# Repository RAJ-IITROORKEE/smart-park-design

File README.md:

<div align="center">

# SmartPark

### A compact ceiling-mounted parking node

XIAO ESP32S3 · Wio-SX1262 LoRa · HC-SR04 · LiPo · optional OLED

**Rev D indoor pilot — digitally checked, awaiting physical validation**

[Download PCB](https://github.com/RAJ-IITROORKEE/smart-park-design/releases/download/revd-pilot/SmartPark-RevD-PCB-Fabrication.zip) · [Download case](https://github.com/RAJ-IITROORKEE/smart-park-design/releases/download/revd-pilot/Case-Print-Files.zip) · [Build guide](docs/SmartPark-RevD-Build-Guide.md) · [3D models](previews/README.md)

**[Watch the product video](https://github.com/RAJ-IITROORKEE/smart-park-design/raw/refs/heads/main/media/showcase/brag.mp4)**

</div>

SmartPark is a hardware design for an indoor parking-bay occupancy node. Mount it above the bay with the ultrasonic faces pointing down; parking firmware can compare the measured distance with an empty-bay baseline and report changes over LoRa. The target installation height is up to **2.8 m**.

This repository contains the carrier PCB, two enclosure variants, editable CAD, fabrication exports and illustrated assembly guides. **Parking firmware, a LoRa gateway and a dashboard are not included.**

## The finished design

| With OLED | Without OLED |
|:---:|:---:|
|  |  |
| Aisle-facing 0.96-inch display and bottom status light pipe | Closed front panel and programmable RGB indication |
| [GLB](previews/04-complete-product/product_oled.glb) · [STEP](previews/04-complete-product/product_oled.step) | [GLB](previews/04-complete-product/product_status.glb) · [STEP](previews/04-complete-product/product_status.step) |

| Carrier PCB | Connected electronics |
|:---:|:---:|
|  |  |
| [PCB GLB](previews/01-pcb/pcb-carrier.glb) · [PCB STEP](previews/01-pcb/pcb-carrier.step) | [Stack GLB](previews/02-connected-electronics/electronics-stack.glb) · [Stack STEP](previews/02-connected-electronics/electronics-stack.step) |

**62 × 50 mm carrier** · **70 × 66 × 50.4 mm closed body** · **94 mm width including mounting ears**

The case conceals the HC-SR04 board and exposes only its two transducer faces underneath, alongside the RGB light pipe. The OLED faces the aisle. These are CAD previews of intended assembly; solder fillets, wiring and some purchased-part details are not modeled.

## Downloads

| What you need | Direct download | Read before use |
|---|---|---|
| PCB manufacturing files | **[Gerbers and drills ZIP](https://github.com/RAJ-IITROORKEE/smart-park-design/releases/download/revd-pilot/SmartPark-RevD-PCB-Fabrication.zip)** | [Board fabrication notes](docs/FABRICATION.md) |
| Case print files | **[STL and 3MF ZIP](https://github.com/RAJ-IITROORKEE/smart-park-design/releases/download/revd-pilot/Case-Print-Files.zip)** | [Part selection and assembly](docs/BUILD_AND_RELEASE.md) |
| Everything together | **[Complete RevD project ZIP](https://github.com/RAJ-IITROORKEE/smart-park-design/releases/download/revd-pilot/SmartPark-RevD-Complete.zip)** | Includes PCB sources, models, guides and videos |
| Illustrated build manual | [Word document](https://github.com/RAJ-IITROORKEE/smart-park-design/raw/refs/heads/main/docs/SmartPark-RevD-Build-Guide.docx) · [Markdown](docs/SmartPark-RevD-Build-Guide.md) | Parts, soldering, wiring, battery and firmware connections |
| Connection schematic | [PNG](outputs/schematics.png) · [PDF](outputs/schematics.pdf) · [SVG](outputs/schematic-svg/SmartMark.svg) | [GPIO map](docs/PINOUT.md) |
| Editable PCB project | [KiCad project folder](hardware) | Open SmartMark.kicad_pro |
| All 3D views | [Organized model index](previews/README.md) | Carrier, electronics, enclosure-only and complete assemblies |

[View the RevD pilot release](https://github.com/RAJ-IITROORKEE/smart-park-design/releases/tag/revd-pilot). File integrity is recorded in [SHA256SUMS.txt](SHA256SUMS.txt).

The same Gerbers serve both variants. For OLED use [BOM.csv](outputs/BOM.csv) and [SMD placements](outputs/placements-smd.csv). For no OLED use [BOM-no-OLED.csv](outputs/BOM-no-OLED.csv) and [matching placements](outputs/placements-smd-no-OLED.csv); omit J2, R8 and R9. A bare fabricated board still needs its electronic parts assembled.

## PCB front and back

| Front copper and silkscreen | Back copper and silkscreen |
|:---:|:---:|
|  |  |
| [Front SVG](previews/01-pcb/pcb-front.svg) · [Assembly SVG](previews/01-pcb/assembly-front.svg) | [Back SVG](previews/01-pcb/pcb-back.svg) · [Assembly SVG](previews/01-pcb/assembly-back.svg) |

Two copper layers, 1.6 mm FR4 and 35 µm nominal copper. **D1 RGB and C7 mount on the underside.** The back preview is mirrored to show the underside; upload fabrication Gerbers and drills unchanged.

## Components

| Qty | Component | Role | Product or ordering reference |
|:---:|---|---|---|
| 1 kit | **XIAO ESP32S3 + Wio-SX1262**, SKU 102010611 | Controller, LoRa radio and battery charging | [Seeed](https://www.seeedstudio.com/Wio-SX1262-with-XIAO-ESP32S3-p-5982.html) · [Robocraze](https://robocraze.com/products/xiao-esp32s3-wio-sx1262-kit-for-meshtastic-lora) |
| 1 | **HC-SR04** | Downward-facing ultrasonic range measurement | [Robu SKU 2444](https://robu.in/product/hc-sr04-ultrasonic-range-finder/) |
| 0 or 1 | **GoldenMorning GME12864-11 OLED** | Optional 0.96-inch 128×64 SSD1306 I²C display | [Robu SKU 617725](https://robu.in/product/0-96-inch-i2c-iic-oled-lcd-module-4pin-with-vcc-gnd-white/) |
| 1 | **Protected 1S LiPo**, target 1500 mAh | 3.7 V battery, within the 51 × 34 × 5 mm reference envelope | [Pack candidate](https://probots.co.in/lithium-ion-rechargeable-battery-3-7v-1500mah-kp-053450.html); confirm total dimensions and protection |
| 1 | **WS2812B-2020-V6**, D1 | Programmable RGB status through a light pipe | [Exact V6 pixel](https://lcscindia.com/part/WS2812B-2020-V6) |
| 1 | **TPS61099DRVR**, U2 | Switched 5 V sensor and RGB supply | [TI](https://www.ti.com/product/TPS61099) |
| 1 | **SN74LVC1G17DBVR**, U4 | Buffers the sensor ECHO into 3.3 V logic | [TI](https://www.ti.com/product/SN74LVC1G17) |
| 1 | **SN74LVC1T45DBVR**, U3 | Translates RGB data to switched 5 V | [TI](https://www.ti.com/product/SN74LVC1T45) |
| 1 | **VLS3012CX-2R2M-1**, L1 | 2.2 µH boost inductor | [TDK](https://product.tdk.com/en/search/inductor/inductor/smd/info?part_no=VLS3012CX-2R2M-1) |
| 1 set | Capacitors, resistors, sockets and cables | Carrier assembly and modular connections | [Complete parts table with links](docs/parts-and-product-links.csv) · [Electrical BOM](docs/BOM.md) |
| optional | **DFRobot FIT0601** regulated solar panel | External regulated 5 V USB input | [DFRobot](https://www.dfrobot.com/product-1774.html) · [Evelta](https://evelta.com/monocrystalline-solar-panel-5v-1a/) |

Product links are sourcing references, not guarantees of stock or sample fit. Confirm the battery, socket/header stack, sensor and display before buying a batch. U2 has a 2 × 2 mm exposed-pad package and needs a controlled reflow process.

## The enclosure

Four releasable snap clips lock the lid. The removable front panel and sensor retainers use screws. Four 4.5 mm mounting holes have **82 × 42 mm** center spacing.

| Version | Installed printed parts |
|---|---|
| **OLED — 7 parts** | base, lid, sensor_mask, sensor_retainer, light_pipe, front_oled, oled_retainer |
| **No OLED — 6 parts** | base, lid, sensor_mask, sensor_retainer, light_pipe, front_blank |
| Trial print | fit_coupon; not installed in the product |

<details>
<summary><strong>See all print parts and enclosure-only CAD</strong></summary>

- [OLED case only — GLB](previews/03-enclosure/case-oled.glb) · [STEP](previews/03-enclosure/case-oled.step)
- [No-OLED case only — GLB](previews/03-enclosure/case-no-oled.glb) · [STEP](previews/03-enclosure/case-no-oled.step)
- [Individual STL files](cad/STL) · [3MF files](cad/3MF) · [Print measurements](docs/PRINT_CHECK.md)

Start with PETG, 0.2 mm layers, a 0.4 mm nozzle and four walls. Print the coupon first, inspect supports in the slicer and keep clip gaps free. Use clear PETG or a suitable 3 mm clear rod for the light pipe. Print individual parts; complete product assemblies include electronics and are not whole-product print files.

</details>

## Power and battery

The LiPo sits **beneath the carrier PCB**, toward the front panel and next to the ultrasonic sensor. Use a protected **3.7 V single cell**, target **1500 mAh** (about 5.55 Wh nominal), within the **51 × 34 × 5 mm** reference envelope, plus 1 mm insulating foam and a nonconductive strap.

**There is no battery socket on the carrier.** Solder a matching protected-pack lead to the XIAO BAT+ and BAT− pads before mating the Wio module. Confirm polarity, PCM dimensions, pouch seals and lead clearance.

External solar support uses a **regulated 5 V USB output into XIAO USB-C**. Use solar or service USB one at a time. The XIAO is the only cell charger; the carrier contains no raw-panel input or MPPT controller.

<details>
<summary><strong>Battery placement image and runtime assumptions</strong></summary>

| Sampling interval | Modelled runtime on 1500 mAh |
|---|---:|
| Every 5 seconds | approximately 12–32 days |
| Every 10 seconds | approximately 23–61 days |

These are unmeasured scenarios with 80% usable capacity, deep sleep, brief sensing and LED flashes, OLED off or omitted, and occasional short LoRa reports. **Continuous RGB keeps the shared sensor supply on** and can reduce the modelled runtime to about 20–40 hours. Wi-Fi, continuous display, radio receive and retries also increase demand.

See [all assumptions and calculations](docs/SmartPark-RevD-Build-Guide.md#estimated-battery-runtime). Seeed lists 50 mA charging on its general XIAO page and 100 mA on the kit page; confirm the delivered board before estimating recharge time. Larger packs or an 18650 require a new fit check or case revision.

</details>

## Wiring and programming

| Function | Connection |
|---|---|
| HC-SR04 TRIG | J1 pin 2 → D0 / GPIO1 |
| HC-SR04 ECHO | J1 pin 3 → U4 buffer → D1 / GPIO2; never raw 5 V ECHO to MCU |
| Sensor supply | J1 pin 1: switched 5V_SENSOR; pin 4: GND |
| Sensor and RGB supply enable | D3 / GPIO4, active high |
| OLED | J2 pins 1 GND, 2 3V3, 3 SCL / GPIO6, 4 SDA / GPIO5 |
| Onboard RGB data | D6 / GPIO43 through U3; one WS2812B-2020-V6 |
| Firmware upload | XIAO USB-C data cable; XIAO ESP32S3 target; disconnect external solar |

Keep BOOST_EN low during startup, initialize TRIG and RGB data low, then enable the supply and wait at least 60 ms before sensing. Leave D2 / GPIO3 unused and reserve D8–D10 for Wio.

The module stack needs two 8.5 mm female sockets, 2.5 mm male header shoulders and a **0.6 mm air gap above the male plastic**, set with a removable soldering shim. Carrier-to-XIAO PCB separation is 11.6 mm; male short legs must be at least 3 mm. Use the XIAO's 14 edge pads, not Wio's radio-only outer rows.

[Full pin orientation](docs/PINOUT.md) · [Connection schematic](outputs/schematics.png) · [Step-by-step build guide](docs/SmartPark-RevD-Build-Guide.md)

## Validation and intended use

| Digital check | Retained result |
|---|---|
| Native KiCad ERC / DRC | 0 reported violations |
| Unrouted connections / schematic parity | 0 / 0 |
| Independent critical package-pin checks | 42 |
| CAD checks | 116; no failures, one unverified commodity sensor dimension assumption |
| Individual printable meshes | 9 closed meshes |
| Source and export integrity | Recorded SHA256 hashes and [delivery check](verification/delivery-check.json) |

Checks apply to the delivered rule configuration, including documented ignored categories. They do not establish physical qualification.

**RevD is an unbuilt indoor pilot.** HC-SR04 has a nominal 4 m range; it is not a 5 m or weatherproof sensor. Calibrate at the actual installation and test different vehicle roofs, adjacent bays, echo timeouts, temperature and mounting angle. Physical fit, electrical startup, RF, battery runtime, latch life and mounting strength still require first-article validation. Resolve India-specific radio settings and equipment requirements before deployment.

## Find your files

| Folder | Contents |
|---|---|
| [hardware](hardware) | Editable KiCad project, schematic, PCB and local libraries |
| [outputs](outputs) | Fabrication exports, schematic images, BOM and placement tables |
| [cad](cad) | Parametric sources, STEP, GLB, STL, 3MF and geometry checks |
| [previews](previews/README.md) | Numbered carrier, electronics, enclosure and full-product previews |
| [docs](docs) | Illustrated Word/Markdown guides, procurement, power and print notes |
| [media](media/README.md) | Showcase video, poster, animation and original recording |
| [verification](verification) | Electrical, mechanical, document and release evidence |

The short showcase was made with [/brag](https://github.com/RAJ-IITROORKEE/smart-park-design/tree/main/media/showcase) and Hyperframes using the real CAD preview images. It presents the design intent, not a demonstration of working deployed hardware.

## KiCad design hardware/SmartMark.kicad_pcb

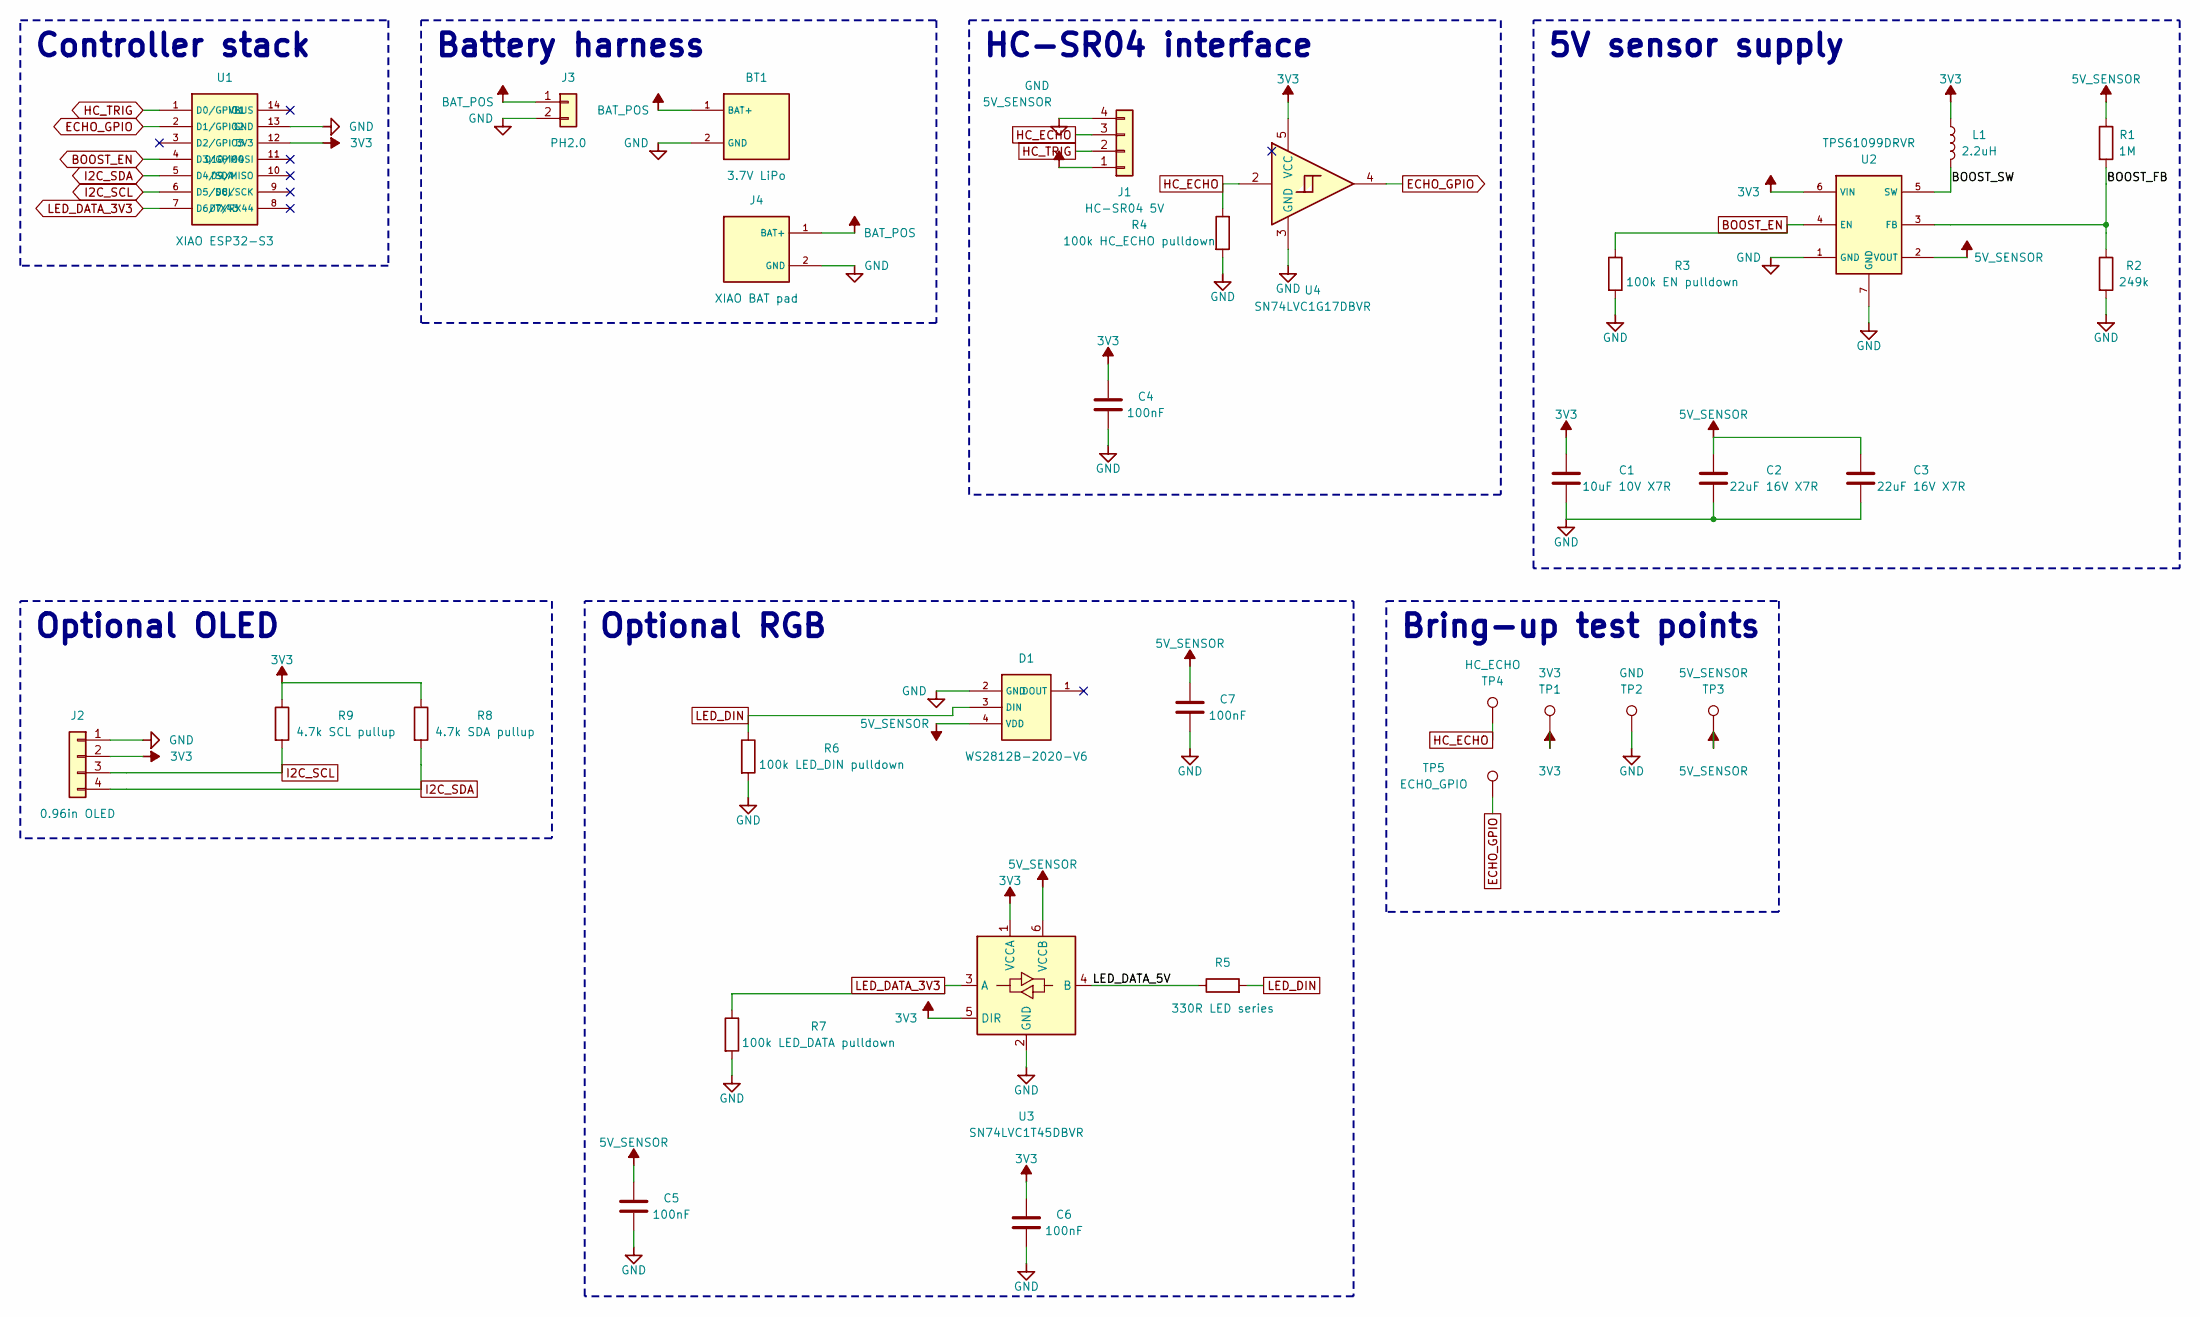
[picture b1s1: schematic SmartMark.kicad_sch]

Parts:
BT1: 3.7V LiPo
C1: 10uF 10V X7R; C_0805_2012Metric
C2, C3: 22uF 16V X7R; C_1206_3216Metric
C4, C5, C6, C7: 100nF; C_0603_1608Metric
D1: WS2812B-2020-V6; WS2812B_2020_V6
J1: HC-SR04 5V; JST_PH_B4B-PH-K_1x04_P2.00mm_Vertical
J2: 0.96in OLED; PinHeader_1x04_P2.54mm_Vertical
J3: PH2.0
J4: XIAO BAT pad
L1: 2.2uH; VLS3012CX_2R2M
R1: 1M; R_0603_1608Metric
R2: 249k; R_0603_1608Metric
R3: 100k EN pulldown; R_0603_1608Metric
R4: 100k HC_ECHO pulldown; R_0603_1608Metric
R5: 330R LED series; R_0603_1608Metric
R6: 100k LED_DIN pulldown; R_0603_1608Metric
R7: 100k LED_DATA pulldown; R_0603_1608Metric
R8: 4.7k SDA pullup; R_0603_1608Metric
R9: 4.7k SCL pullup; R_0603_1608Metric
TP1: 3V3; TestPoint_Pad_D1.0mm
TP2: GND; TestPoint_Pad_D1.0mm
TP3: 5V_SENSOR; TestPoint_Pad_D1.0mm
TP4: HC_ECHO; TestPoint_Pad_D1.0mm
TP5: ECHO_GPIO; TestPoint_Pad_D1.0mm
U1: XIAO ESP32-S3; XIAO_S3_STACK_SOCKET_2x7
U2: TPS61099DRVR; WSON-6-1EP_2x2mm_P0.65mm_EP1x1.6mm
U3: SN74LVC1T45DBVR; SOT-23-6
U4: SN74LVC1G17DBVR; SOT-23-5

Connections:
3V3: C1.1, C4.1, C6.1, J2.2, L1.1, R8.1, R9.1, TP1.1, U1.12 (3V3), U2.6 (VIN), U3.1 (VCCA), U3.5 (DIR), U4.5 (VCC)
5V_SENSOR: C2.1, C3.1, C5.1, C7.1, D1.4 (VDD), J1.1, R1.1, TP3.1, U2.2 (VOUT), U3.6 (VCCB)
/BOOST_FB: R1.2, R2.1, U2.3 (FB)
/BOOST_SW: L1.2, U2.5 (SW)
/LED_DATA_5V: R5.1, U3.4 (B)
BOOST_EN: R3.1, U1.4 (D3/GPIO4), U2.4 (EN)
ECHO_GPIO: TP5.1, U1.2 (D1/GPIO2), U4.4
GND: BT1.2 (GND), C1.2, C2.2, C3.2, C4.2, C5.2, C6.2, C7.2, D1.2 (GND), J1.4, J2.1, J3.2, J4.2 (GND), R2.2, R3.2, R4.2, R6.2, R7.2, TP2.1, U1.13 (GND), U2.1 (GND), U2.7 (GND), U3.2 (GND), U4.3 (GND)
HC_ECHO: J1.3, R4.1, TP4.1, U4.2
HC_TRIG: J1.2, U1.1 (D0/GPIO1)
I2C_SCL: J2.3, R9.2, U1.6 (D5/SCL)
I2C_SDA: J2.4, R8.2, U1.5 (D4/SDA)
LED_DATA_3V3: R7.1, U1.7 (D6/TX43), U3.3 (A)
LED_DIN: D1.3 (DIN), R5.2, R6.1
unnamed: BT1.1 (BAT+), J3.1, J4.1 (BAT+)

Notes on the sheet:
5V sensor supply
Battery harness
Bring-up test points
Controller stack
HC-SR04 interface
Optional OLED
Optional RGB

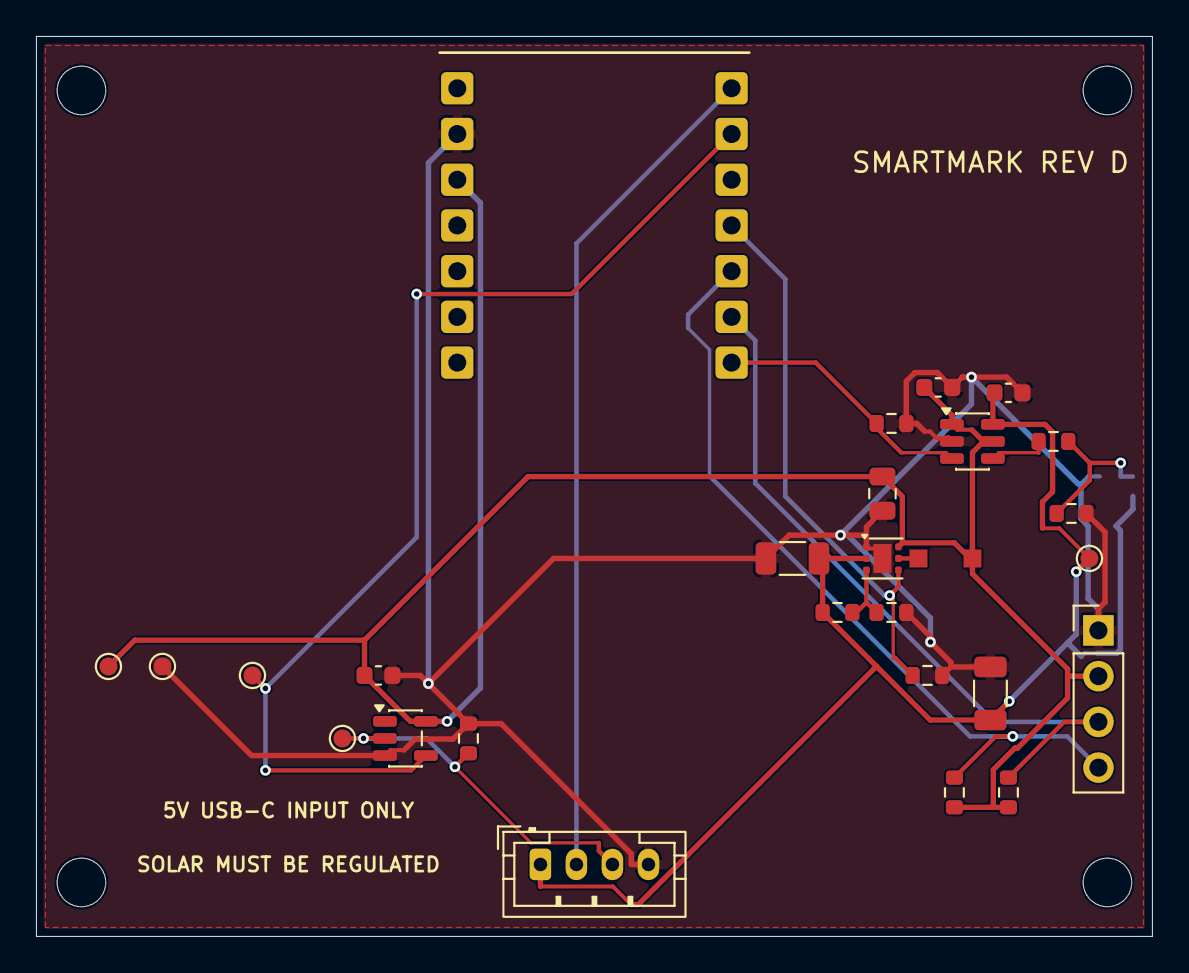
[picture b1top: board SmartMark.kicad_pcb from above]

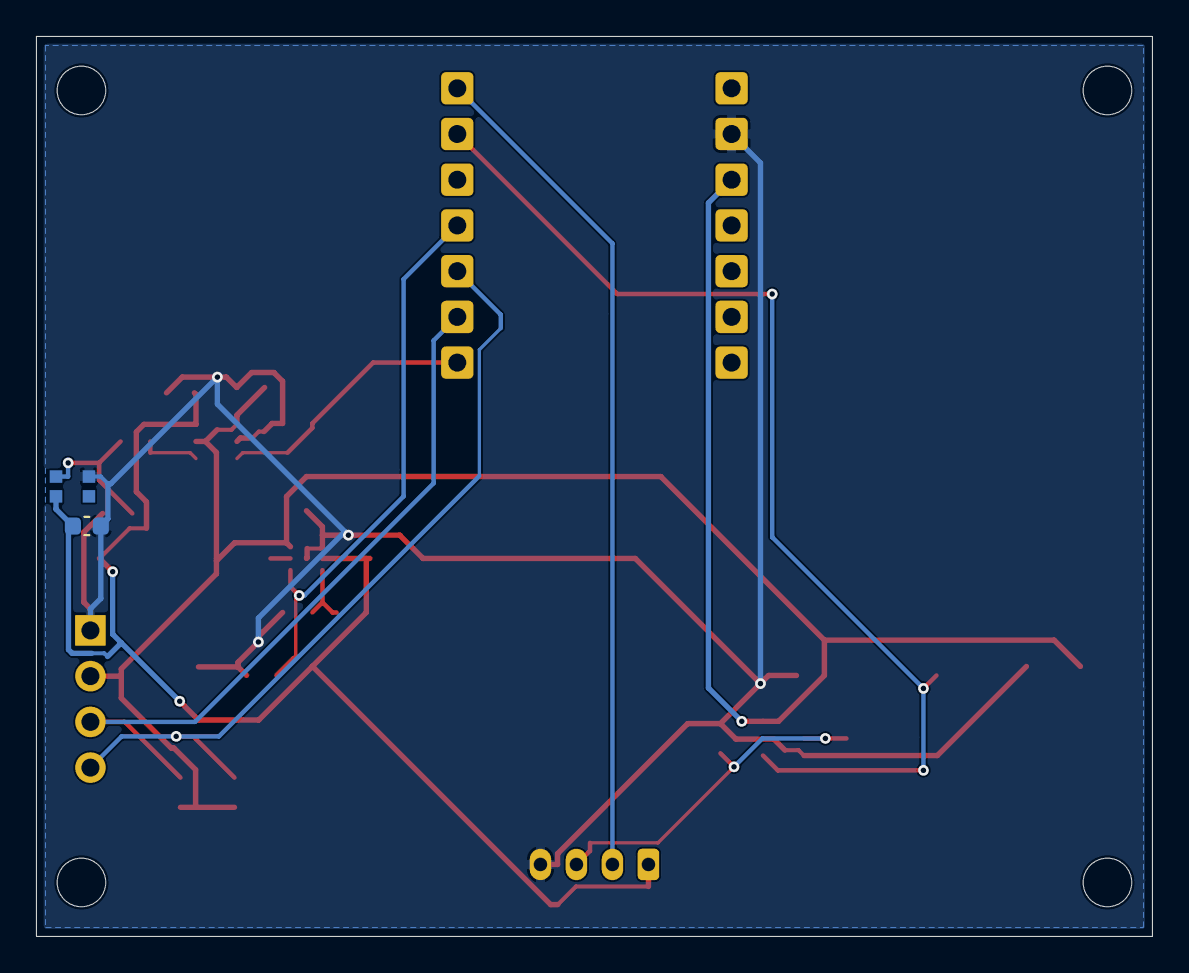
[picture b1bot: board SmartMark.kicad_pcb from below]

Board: 2 copper layers, 62.0 x 50.0 mm, 33 parts (2 on the bottom side), 14 nets.

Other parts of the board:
H1, H2, H3, H4: M2.5; MountingHole_2.7mm

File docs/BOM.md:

# Bill of materials

Electrical BOM; generic passives are specified by value and size. Unselected MPNs remain procurement gates.

| Refdes | Value | Footprint | MPN / status | Notes |
|---|---|---|---|---|
| U1 | XIAO ESP32-S3 | SmartMark:XIAO_S3_STACK_SOCKET_2x7 | Seeed module stack | Carrier mounting is two 1×7 2.54 mm female sockets, 8.5 mm high; mate the XIAO edge pads through 2.5 mm-shoulder male headers with a 0.6 mm air gap above the plastic (11.6 mm total carrier-to-XIAO plane separation). Seeed module stack is off-carrier and not SMT-placed. |
| BT1 | 3.7V LiPo |  | Protected pack MPN not frozen; confirm protection | Protected 1S LiPo pack with JST-PH2 pigtail. Off-board; verify a real protection circuit and pack polarity. |
| J3 | PH2.0 |  | Off-board JST-PH2 pigtail | Battery pack's PH2 cable connector, off-board; mating and continuity checks required. |
| J4 | XIAO BAT pad |  | XIAO underside pads (symbol only) | Symbolic contact to XIAO underside BAT pads; not a PCB-mounted connector. |
| U2 | TPS61099DRVR | Package_SON:WSON-6-1EP_2x2mm_P0.65mm_EP1x1.6mm | TPS61099DRVR | TI TPS61099DRVR; adjustable 5 V boost. |
| U3 | SN74LVC1T45DBVR | Package_TO_SOT_SMD:SOT-23-6 | SN74LVC1T45DBVR | TI SN74LVC1T45DBVR; 3.3-to-switched-5 V RGB data translation. |
| U4 | SN74LVC1G17DBVR | Package_TO_SOT_SMD:SOT-23-5 | SN74LVC1G17DBVR | TI SN74LVC1G17DBVR; 5.5 V tolerant sensor echo buffer. |
| J1 | HC-SR04 5V | Connector_JST:JST_PH_B4B-PH-K_1x04_P2.00mm_Vertical | UNSELECTED generic value | JST-PH sensor cable; confirm actual harness pin continuity. |
| J2 | 0.96in OLED | Connector_PinHeader_2.54mm:PinHeader_1x04_P2.54mm_Vertical | GoldenMorning GME12864-11 (Robu SKU 617725; optional display) | Optional GoldenMorning GME12864-11 0.96-inch OLED (Robu SKU 617725); connect by cable, not a carrier-mounted display. |
| D1 | WS2812B-2020-V6 | SmartMark:WS2812B_2020_V6 | WS2812B-2020-V6 | Worldsemi WS2812B-2020-V6; custom pads follow the official package-top drawing; it is flipped to B.Cu for the case-floor light pipe. |
| L1 | 2.2uH | SmartMark:VLS3012CX_2R2M | TDK VLS3012CX-2R2M-1 | TDK VLS3012CX-2R2M-1; TDK 3×3×1.2 mm part, 1.7 A max inductance-change rating; local 1.0 mm land pads on 3.0 mm centers. |
| C1 | 10uF 10V X7R | Capacitor_SMD:C_0805_2012Metric | GRM21BR71A106KE51L | Murata GRM21BR71A106KE51L; 10 µF, 10 V, X7R, 0805 boost input bypass. |
| C2 | 22uF 16V X7R | Capacitor_SMD:C_1206_3216Metric | GRM31CZ71C226ME15L | Murata GRM31CZ71C226ME15L; 22 µF, 16 V, X7R, 1206 boost output capacitor. |
| C3 | 22uF 16V X7R | Capacitor_SMD:C_1206_3216Metric | GRM31CZ71C226ME15L | Murata GRM31CZ71C226ME15L; 22 µF, 16 V, X7R, 1206 boost output capacitor. |
| C4 | 100nF | Capacitor_SMD:C_0603_1608Metric | UNSELECTED generic value | 100 nF local bypass for the SN74LVC1G17 sensor buffer. |
| C5 | 100nF | Capacitor_SMD:C_0603_1608Metric | UNSELECTED generic value | 100 nF local bypass for SN74LVC1T45 VCCB (switched 5 V). |
| C6 | 100nF | Capacitor_SMD:C_0603_1608Metric | UNSELECTED generic value | 100 nF local bypass for SN74LVC1T45 VCCA (3.3 V). |
| C7 | 100nF | Capacitor_SMD:C_0603_1608Metric | UNSELECTED generic value | 100 nF local 5 V bypass adjacent to the bottom-side RGB pixel. |
| R1 | 1M | Resistor_SMD:R_0603_1608Metric | UNSELECTED generic value | Generic passive; confirm effective value and rating at bias. |
| R2 | 249k | Resistor_SMD:R_0603_1608Metric | UNSELECTED generic value | Generic passive; confirm effective value and rating at bias. |
| R3 | 100k EN pulldown | Resistor_SMD:R_0603_1608Metric | UNSELECTED generic value | Generic passive; confirm effective value and rating at bias. |
| R4 | 100k HC_ECHO pulldown | Resistor_SMD:R_0603_1608Metric | UNSELECTED generic value | Generic passive; confirm effective value and rating at bias. |
| R5 | 330R LED series | Resistor_SMD:R_0603_1608Metric | UNSELECTED generic value | Generic passive; confirm effective value and rating at bias. |
| R6 | 100k LED_DIN pulldown | Resistor_SMD:R_0603_1608Metric | UNSELECTED generic value | Generic passive; confirm effective value and rating at bias. |
| R7 | 100k LED_DATA pulldown | Resistor_SMD:R_0603_1608Metric | UNSELECTED generic value | Generic passive; confirm effective value and rating at bias. |
| R8 | 4.7k SDA pullup | Resistor_SMD:R_0603_1608Metric | UNSELECTED generic value | Generic passive; confirm effective value and rating at bias. |
| R9 | 4.7k SCL pullup | Resistor_SMD:R_0603_1608Metric | UNSELECTED generic value | Generic passive; confirm effective value and rating at bias. |
| TP1 | 3V3 | TestPoint:TestPoint_Pad_D1.0mm | test pad | 3V3 bare copper test pad. |
| TP2 | GND | TestPoint:TestPoint_Pad_D1.0mm | test pad | GND bare copper test pad. |
| TP3 | 5V_SENSOR | TestPoint:TestPoint_Pad_D1.0mm | test pad | 5V_SENSOR bare copper test pad. |
| TP4 | HC_ECHO | TestPoint:TestPoint_Pad_D1.0mm | test pad | HC_ECHO bare copper test pad. |
| TP5 | ECHO_GPIO | TestPoint:TestPoint_Pad_D1.0mm | test pad | ECHO_GPIO bare copper test pad. |

U1 is a socket interface: fit two 1×7 2.54 mm female sockets (8.5 mm body height) on the carrier and mating male headers with a 2.5 mm shoulder and at least 3 mm short legs on the XIAO edge pads. Use a removable 0.6 mm soldering shim to leave air above the shoulder; remove it after soldering. This clears the USB anchors and gives 11.6 mm total separation. The assembled XIAO ESP32-S3/Wio-SX1262 stack plugs into the carrier; do not SMT-place the Seeed module as a PCB component. Verify the actual socket/header heights and sample fit before release.
BT1/J3/J4 are off-board battery components and contacts; do not place them on the carrier. Verify pack protection, polarity and continuity; HC-SR04 module/revision and cable; OLED unit fit; and TDK land-pattern compatibility with the chosen assembly process. Capacitor bias estimates are typical supplier curves and need board-level startup/transient validation.

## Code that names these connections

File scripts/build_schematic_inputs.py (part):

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    {"ref": "TP2", "libId": "Connector:TestPoint", "value": "GND", "footprint": "TestPoint:TestPoint_Pad_D1.0mm", "group": "Bring-up test points"},
    {"ref": "TP3", "libId": "Connector:TestPoint", "value": "5V_SENSOR", "footprint": "TestPoint:TestPoint_Pad_D1.0mm", "group": "Bring-up test points"},
    {"ref": "TP4", "libId": "Connector:TestPoint", "value": "HC_ECHO", "footprint": "TestPoint:TestPoint_Pad_D1.0mm", "group": "Bring-up test points"},
    {"ref": "TP5", "libId": "Connector:TestPoint", "value": "ECHO_GPIO", "footprint": "TestPoint:TestPoint_Pad_D1.0mm", "group": "Bring-up test points"},
]

NETS = [
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    {"name": "3V3", "kind": "power", "pins": ["U1.12", "U2.6", "U3.1", "U3.5", "U4.5", "J2.2", "L1.1", "C1.1", "C4.1", "C6.1", "R8.1", "R9.1", "TP1.1"]},
    {"name": "GND", "kind": "ground", "pins": ["BT1.2", "J3.2", "J4.2", "U1.13", "U2.1", "U2.7", "U3.2", "U4.3", "J1.4", "J2.1", "D1.2", "C1.2", "C2.2", "C3.2", "C4.2", "C5.2", "C6.2", "C7.2", "R2.2", "R3.2", "R4.2", "R6.2", "R7.2", "TP2.1"]},
    {"name": "5V_SENSOR", "kind": "power", "pins": ["U2.2", "U3.6", "J1.1", "D1.4", "C2.1", "C3.1", "C5.1", "C7.1", "R1.1", "TP3.1"]},
    {"name": "BOOST_SW", "kind": "signal", "pins": ["U2.5", "L1.2"]},
    {"name": "BOOST_FB", "kind": "signal", "pins": ["U2.3", "R1.2", "R2.1"]},
    {"name": "BOOST_EN", "kind": "signal", "pins": ["U2.4", "U1.4", "R3.1"]},
    {"name": "HC_TRIG", "kind": "signal", "pins": ["U1.1", "J1.2"]},
    {"name": "HC_ECHO", "kind": "signal", "pins": ["J1.3", "U4.2", "R4.1", "TP4.1"]},
    {"name": "ECHO_GPIO", "kind": "signal", "pins": ["U4.4", "U1.2", "TP5.1"]},
    {"name": "I2C_SDA", "kind": "signal", "pins": ["U1.5", "J2.4", "R8.2"]},
    {"name": "I2C_SCL", "kind": "signal", "pins": ["U1.6", "J2.3", "R9.2"]},
    {"name": "LED_DATA_3V3", "kind": "signal", "pins": ["U1.7", "U3.3", "R7.1"]},
    {"name": "LED_DATA_5V", "kind": "signal", "pins": ["U3.4", "R5.1"]},
    {"name": "LED_DIN", "kind": "signal", "pins": ["R5.2", "D1.3", "R6.1"]},
]

NO_CONNECTS = ["U1.3", "U1.8", "U1.9", "U1.10", "U1.11", "U1.14", "U4.1", "D1.1"]
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
def custom_symbols() -> str:
    body = ["\t\t(rectangle (start -5.08 10.16) (end 5.08 -10.16) (stroke (width 0.254) (type default)) (fill (type background)))"]
    left = [(1, "D0/GPIO1"), (2, "D1/GPIO2"), (3, "D2/GPIO3"), (4, "D3/GPIO4"), (5, "D4/SDA"), (6, "D5/SCL"), (7, "D6/TX43")]
    right = [(14, "VBUS"), (13, "GND"), (12, "3V3"), (11, "D10/MOSI"), (10, "D9/MISO"), (9, "D8/SCK"), (8, "D7/RX44")]
    for i, (num, name) in enumerate(left):
        body.append(symbol_pin(num, name, "bidirectional", -10.16, 7.62 - 2.54 * i, 0))
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
| Carrier net | XIAO pad | Signal | GPIO | Use |
|---|---:|---|---:|---|
| HC_TRIG | 1 | D0 | GPIO1 | Sensor trigger |
| ECHO_GPIO | 2 | D1 | GPIO2 | Buffered sensor echo |
| NC | 3 | D2 | GPIO3 | Reserved; ESP32-S3 strapping pin |
| BOOST_EN | 4 | D3 | GPIO4 | Boost enable, active high |
| I2C_SDA | 5 | D4/SDA | GPIO5 | Optional OLED |
| I2C_SCL | 6 | D5/SCL | GPIO6 | Optional OLED |
| LED_DATA_3V3 | 7 | D6/TX | GPIO43 | RGB data; UART0 TX during boot |
| NC | 8 | D7/RX | GPIO44 | Reserved |
| NC | 9 | D8/SCK | GPIO7 | Wio radio SPI reserved |
| NC | 10 | D9/MISO | GPIO8 | Wio radio SPI reserved |
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
At reset, keep BOOST_EN low and initialize GPIO43/D6 low before turning on 5V_SENSOR. GPIO43 is UART0 TX during boot; GPIO3/D2 is an ESP32-S3 strapping pin and remains unused. Wait at least 60 ms after enabling the sensor/pixel supply before the first HC-SR04 measurement cycle.

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"""
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        "C7": "100 nF local 5 V bypass adjacent to the bottom-side RGB pixel.",
        "TP1": "3V3 bare copper test pad.", "TP2": "GND bare copper test pad.",
        "TP3": "5V_SENSOR bare copper test pad.", "TP4": "HC_ECHO bare copper test pad.",
        "TP5": "ECHO_GPIO bare copper test pad.",
    }
    lines = ["# Bill of materials", "", "Electrical BOM; generic passives are specified by value and size. Unselected MPNs remain procurement gates.", "", "| Refdes | Value | Footprint | MPN / status | Notes |", "|---|---|---|---|---|"]
    for part in PARTS:
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
## HC-SR04 interface

J1 carries 5V_SENSOR, TRIG, ECHO, and GND. U4 buffers the module echo to 3.3 V GPIO; XIAO D0/GPIO1 drives the trigger directly.

## 5V sensor supply

U2 boosts 3V3 to a GPIO4-enabled 5V_SENSOR rail for the sensor and optional RGB pixel, with TI reference feedback and bypassing.

## Optional OLED

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
## Bring-up test points

TP1–TP5 expose 3V3, GND, 5V_SENSOR, HC_ECHO, and ECHO_GPIO during controlled validation.
"""


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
